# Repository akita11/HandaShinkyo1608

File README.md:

# Handa Shinkyo 1608

Ken Nakagakiさん(@ken0324)さんの[半田心経](https://x.com/i/events/1101723254899834880)を参考に、はんだ付けのしやすい1608サイズ（インチ表記で0603サイズ）のチップ抵抗を使った半田心経基板です。1-2Ωのチップ抵抗276個とLEDを1個はんだづけして完成です。（LEDの向きに注意。小さい緑マーカがある側が、USB-C基板コネクタ側です）

部品リストとPCBA用の部品位置ファイルもあり、そのまま[JLCPCB](https://www.jlcpcb.com)にPCBA発注することもできます（チート）。

給電は、裏面のボタン電池(CR2032)または基板パターンを使ったUSB Type-Cで行います（※USB Type-Cコネクタ給電を使う場合は板厚0.6mで製造）。
（USB PD規格のACアダプタ等を使う場合は、裏面に5.1kΩの抵抗2個をとりつけます）

はんだ付けのお勤めをとおして心を安らげましょう。合掌。

ハッシュタグ: #半田心経

## Author

Junichi Akita (@akita11, akita@ifdl.jp)

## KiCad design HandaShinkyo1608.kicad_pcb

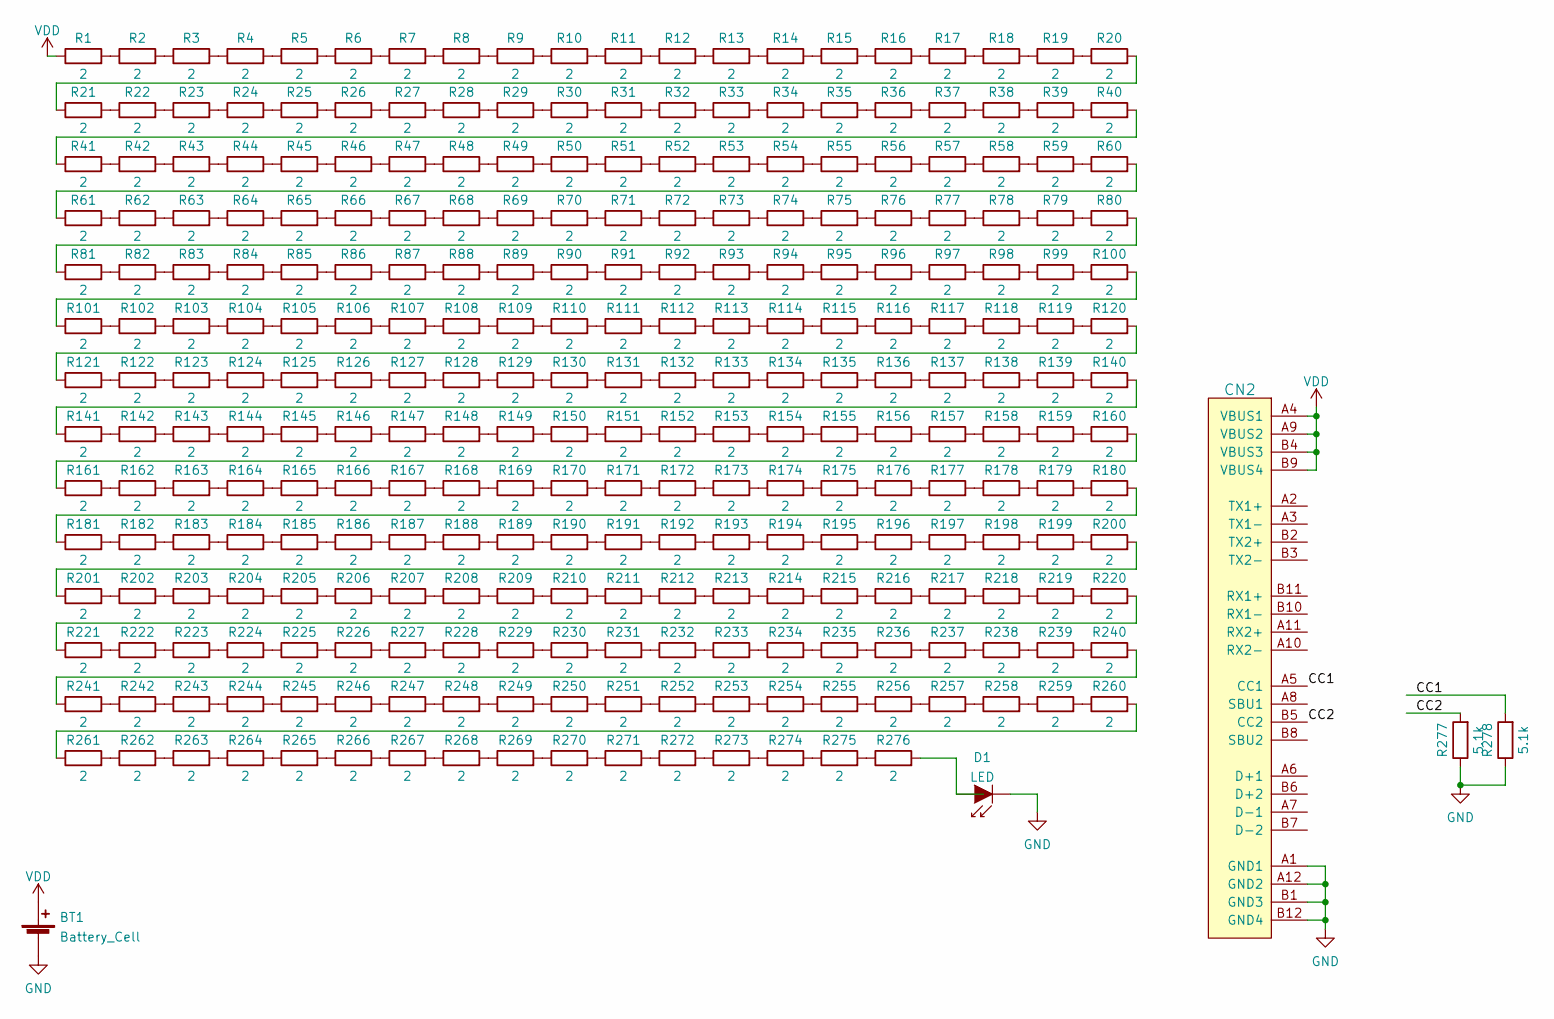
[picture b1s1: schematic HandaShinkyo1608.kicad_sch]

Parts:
BT1: Battery_Cell; BAT_CR2032_BC-2001
CN2: CON_USB-CPCBPLUG; USB-C_PCBPLUG
D1: LED; LED_0603_1608Metric
R1, R2, R3, R4, R5, R6, R7, R8, R9, R10, R11, R12, R13, R14, R15, R16, R17, R18, R19, R20, R21, R22, R23, R24, R25, R26, R27, R28, R29, R30, R31, R32, R33, R34, R35, R36, R37, R38, R39, R40, R41, R42, R43, R44, R45, R46, R47, R48, R49, R50, R51, R52, R53, R54, R55, R56, R57, R58, R59, R60, R61, R62, R63, R64, R65, R66, R67, R68, R69, R70, R71, R72, R73, R74, R75, R76, R77, R78, R79, R80, R81, R82, R83, R84, R85, R86, R87, R88, R89, R90, R91, R92, R93, R94, R95, R96, R97, R98, R99, R100, R101, R102, R103, R104, R105, R106, R107, R108, R109, R110, R111, R112, R113, R114, R115, R116, R117, R118, R119, R120, R121, R122, R123, R124, R125, R126, R127, R128, R129, R130, R131, R132, R133, R134, R135, R136, R137, R138, R139, R140, R141, R142, R143, R144, R145, R146, R147, R148, R149, R150, R151, R152, R153, R154, R155, R156, R157, R158, R159, R160, R161, R162, R163, R164, R165, R166, R167, R168, R169, R170, R171, R172, R173, R174, R175, R176, R177, R178, R179, R180, R181, R182, R183, R184, R185, R186, R187, R188, R189, R190, R191, R192, R193, R194, R195, R196, R197, R198, R199, R200, R201, R202, R203, R204, R205, R206, R207, R208, R209, R210, R211, R212, R213, R214, R215, R216, R217, R218, R219, R220, R221, R222, R223, R224, R225, R226, R227, R228, R229, R230, R231, R232, R233, R234, R235, R236, R237, R238, R239, R240, R241, R242, R243, R244, R245, R246, R247, R248, R249, R250, R251, R252, R253, R254, R255, R256, R257, R258, R259, R260, R261, R262, R263, R264, R265, R266, R267, R268, R269, R270, R271, R272, R273, R274, R275, R276: 2; R_0603_1608Metric
R277, R278: 5.1k; R_0603_1608Metric

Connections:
/CC1: CN2.A5 (CC1), R278.2
/CC2: CN2.B5 (CC2), R277.2
unnamed: D1.2 (A), R276.2
unnamed: R1.2, R2.1
unnamed: R2.2, R3.1
unnamed: R3.2, R4.1
unnamed: R4.2, R5.1
unnamed: R5.2, R6.1
unnamed: R6.2, R7.1
unnamed: R7.2, R8.1
unnamed: R8.2, R9.1
unnamed: R9.2, R10.1
unnamed: R10.2, R11.1
unnamed: R11.2, R12.1
unnamed: R12.2, R13.1
unnamed: R13.2, R14.1
unnamed: R14.2, R15.1
unnamed: R15.2, R16.1
unnamed: R16.2, R17.1
unnamed: R17.2, R18.1
unnamed: R18.2, R19.1
unnamed: R19.2, R20.1
unnamed: R20.2, R21.1
unnamed: R21.2, R22.1
unnamed: R22.2, R23.1
unnamed: R23.2, R24.1
unnamed: R24.2, R25.1
unnamed: R25.2, R26.1
unnamed: R26.2, R27.1
unnamed: R27.2, R28.1
unnamed: R28.2, R29.1
unnamed: R29.2, R30.1
unnamed: R30.2, R31.1
unnamed: R31.2, R32.1
unnamed: R32.2, R33.1
unnamed: R33.2, R34.1
unnamed: R34.2, R35.1
unnamed: R35.2, R36.1
unnamed: R36.2, R37.1
unnamed: R37.2, R38.1
unnamed: R38.2, R39.1
unnamed: R39.2, R40.1
unnamed: R40.2, R41.1
unnamed: R41.2, R42.1
unnamed: R42.2, R43.1
unnamed: R43.2, R44.1
unnamed: R44.2, R45.1
unnamed: R45.2, R46.1
unnamed: R46.2, R47.1
unnamed: R47.2, R48.1
unnamed: R48.2, R49.1
unnamed: R49.2, R50.1
unnamed: R50.2, R51.1
unnamed: R51.2, R52.1
unnamed: R52.2, R53.1
unnamed: R53.2, R54.1
unnamed: R54.2, R55.1
unnamed: R55.2, R56.1
unnamed: R56.2, R57.1
unnamed: R57.2, R58.1
unnamed: R58.2, R59.1
unnamed: R59.2, R60.1
unnamed: R60.2, R61.1
unnamed: R61.2, R62.1
unnamed: R62.2, R63.1
unnamed: R63.2, R64.1
unnamed: R64.2, R65.1
unnamed: R65.2, R66.1
unnamed: R66.2, R67.1
unnamed: R67.2, R68.1
unnamed: R68.2, R69.1
unnamed: R69.2, R70.1
unnamed: R70.2, R71.1
unnamed: R71.2, R72.1
unnamed: R72.2, R73.1
unnamed: R73.2, R74.1
unnamed: R74.2, R75.1
unnamed: R75.2, R76.1
unnamed: R76.2, R77.1
unnamed: R77.2, R78.1
unnamed: R78.2, R79.1
unnamed: R79.2, R80.1
unnamed: R80.2, R81.1
unnamed: R81.2, R82.1
unnamed: R82.2, R83.1
unnamed: R83.2, R84.1
unnamed: R84.2, R85.1
unnamed: R85.2, R86.1
unnamed: R86.2, R87.1
unnamed: R87.2, R88.1
unnamed: R88.2, R89.1
unnamed: R89.2, R90.1
unnamed: R90.2, R91.1
unnamed: R91.2, R92.1
unnamed: R92.2, R93.1
unnamed: R93.2, R94.1
unnamed: R94.2, R95.1
unnamed: R95.2, R96.1
unnamed: R96.2, R97.1
unnamed: R97.2, R98.1
unnamed: R98.2, R99.1
unnamed: R99.2, R100.1
unnamed: R100.2, R101.1
unnamed: R101.2, R102.1
unnamed: R102.2, R103.1
unnamed: R103.2, R104.1
unnamed: R104.2, R105.1
unnamed: R105.2, R106.1
unnamed: R106.2, R107.1
unnamed: R107.2, R108.1
unnamed: R108.2, R109.1
unnamed: R109.2, R110.1
unnamed: R110.2, R111.1
unnamed: R111.2, R112.1
unnamed: R112.2, R113.1
unnamed: R113.2, R114.1
unnamed: R114.2, R115.1
unnamed: R115.2, R116.1
unnamed: R116.2, R117.1
unnamed: R117.2, R118.1
unnamed: R118.2, R119.1
unnamed: R119.2, R120.1
unnamed: R120.2, R121.1
unnamed: R121.2, R122.1
unnamed: R122.2, R123.1
unnamed: R123.2, R124.1
unnamed: R124.2, R125.1
unnamed: R125.2, R126.1
unnamed: R126.2, R127.1
unnamed: R127.2, R128.1
unnamed: R128.2, R129.1
unnamed: R129.2, R130.1
unnamed: R130.2, R131.1
unnamed: R131.2, R132.1
unnamed: R132.2, R133.1
unnamed: R133.2, R134.1
unnamed: R134.2, R135.1
unnamed: R135.2, R136.1
unnamed: R136.2, R137.1
unnamed: R137.2, R138.1
unnamed: R138.2, R139.1
unnamed: R139.2, R140.1
unnamed: R140.2, R141.1
unnamed: R141.2, R142.1
unnamed: R142.2, R143.1
unnamed: R143.2, R144.1
unnamed: R144.2, R145.1
unnamed: R145.2, R146.1
unnamed: R146.2, R147.1
unnamed: R147.2, R148.1
unnamed: R148.2, R149.1
unnamed: R149.2, R150.1
unnamed: R150.2, R151.1
unnamed: R151.2, R152.1
unnamed: R152.2, R153.1
unnamed: R153.2, R154.1
unnamed: R154.2, R155.1
unnamed: R155.2, R156.1
unnamed: R156.2, R157.1
unnamed: R157.2, R158.1
unnamed: R158.2, R159.1
unnamed: R159.2, R160.1
unnamed: R160.2, R161.1
unnamed: R161.2, R162.1
unnamed: R162.2, R163.1
unnamed: R163.2, R164.1
unnamed: R164.2, R165.1
unnamed: R165.2, R166.1
unnamed: R166.2, R167.1
unnamed: R167.2, R168.1
unnamed: R168.2, R169.1
unnamed: R169.2, R170.1
unnamed: R170.2, R171.1
unnamed: R171.2, R172.1
unnamed: R172.2, R173.1
unnamed: R173.2, R174.1
unnamed: R174.2, R175.1
unnamed: R175.2, R176.1
unnamed: R176.2, R177.1
unnamed: R177.2, R178.1
unnamed: R178.2, R179.1
unnamed: R179.2, R180.1
unnamed: R180.2, R181.1
unnamed: R181.2, R182.1
unnamed: R182.2, R183.1
unnamed: R183.2, R184.1
unnamed: R184.2, R185.1
unnamed: R185.2, R186.1
unnamed: R186.2, R187.1
unnamed: R187.2, R188.1
unnamed: R188.2, R189.1
unnamed: R189.2, R190.1
unnamed: R190.2, R191.1
unnamed: R191.2, R192.1
unnamed: R192.2, R193.1
unnamed: R193.2, R194.1
unnamed: R194.2, R195.1
unnamed: R195.2, R196.1
unnamed: R196.2, R197.1
unnamed: R197.2, R198.1
unnamed: R198.2, R199.1
unnamed: R199.2, R200.1
unnamed: R200.2, R201.1
unnamed: R201.2, R202.1
unnamed: R202.2, R203.1
unnamed: R203.2, R204.1
unnamed: R204.2, R205.1
unnamed: R205.2, R206.1
unnamed: R206.2, R207.1
unnamed: R207.2, R208.1
unnamed: R208.2, R209.1
unnamed: R209.2, R210.1
unnamed: R210.2, R211.1
unnamed: R211.2, R212.1
unnamed: R212.2, R213.1
unnamed: R213.2, R214.1
unnamed: R214.2, R215.1
unnamed: R215.2, R216.1
unnamed: R216.2, R217.1
unnamed: R217.2, R218.1
unnamed: R218.2, R219.1
unnamed: R219.2, R220.1
unnamed: R220.2, R221.1
unnamed: R221.2, R222.1
unnamed: R222.2, R223.1
unnamed: R223.2, R224.1
unnamed: R224.2, R225.1
unnamed: R225.2, R226.1
unnamed: R226.2, R227.1
unnamed: R227.2, R228.1
unnamed: R228.2, R229.1
unnamed: R229.2, R230.1
unnamed: R230.2, R231.1
unnamed: R231.2, R232.1
unnamed: R232.2, R233.1
unnamed: R233.2, R234.1
unnamed: R234.2, R235.1
unnamed: R235.2, R236.1
unnamed: R236.2, R237.1
unnamed: R237.2, R238.1
unnamed: R238.2, R239.1
unnamed: R239.2, R240.1
unnamed: R240.2, R241.1
unnamed: R241.2, R242.1
unnamed: R242.2, R243.1
unnamed: R243.2, R244.1
unnamed: R244.2, R245.1
unnamed: R245.2, R246.1
unnamed: R246.2, R247.1
unnamed: R247.2, R248.1
unnamed: R248.2, R249.1
unnamed: R249.2, R250.1
unnamed: R250.2, R251.1
unnamed: R251.2, R252.1
unnamed: R252.2, R253.1
unnamed: R253.2, R254.1
unnamed: R254.2, R255.1
unnamed: R255.2, R256.1
unnamed: R256.2, R257.1
unnamed: R257.2, R258.1
unnamed: R258.2, R259.1
unnamed: R259.2, R260.1
unnamed: R260.2, R261.1
unnamed: R261.2, R262.1
unnamed: R262.2, R263.1
unnamed: R263.2, R264.1
unnamed: R264.2, R265.1
unnamed: R265.2, R266.1
unnamed: R266.2, R267.1
unnamed: R267.2, R268.1
unnamed: R268.2, R269.1
unnamed: R269.2, R270.1
unnamed: R270.2, R271.1
unnamed: R271.2, R272.1
unnamed: R272.2, R273.1
unnamed: R273.2, R274.1
unnamed: R274.2, R275.1
unnamed: R275.2, R276.1
VDD: BT1.1 (+), CN2.A4 (VBUS1), CN2.A9 (VBUS2), CN2.B4 (VBUS3), CN2.B9 (VBUS4), R1.1

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
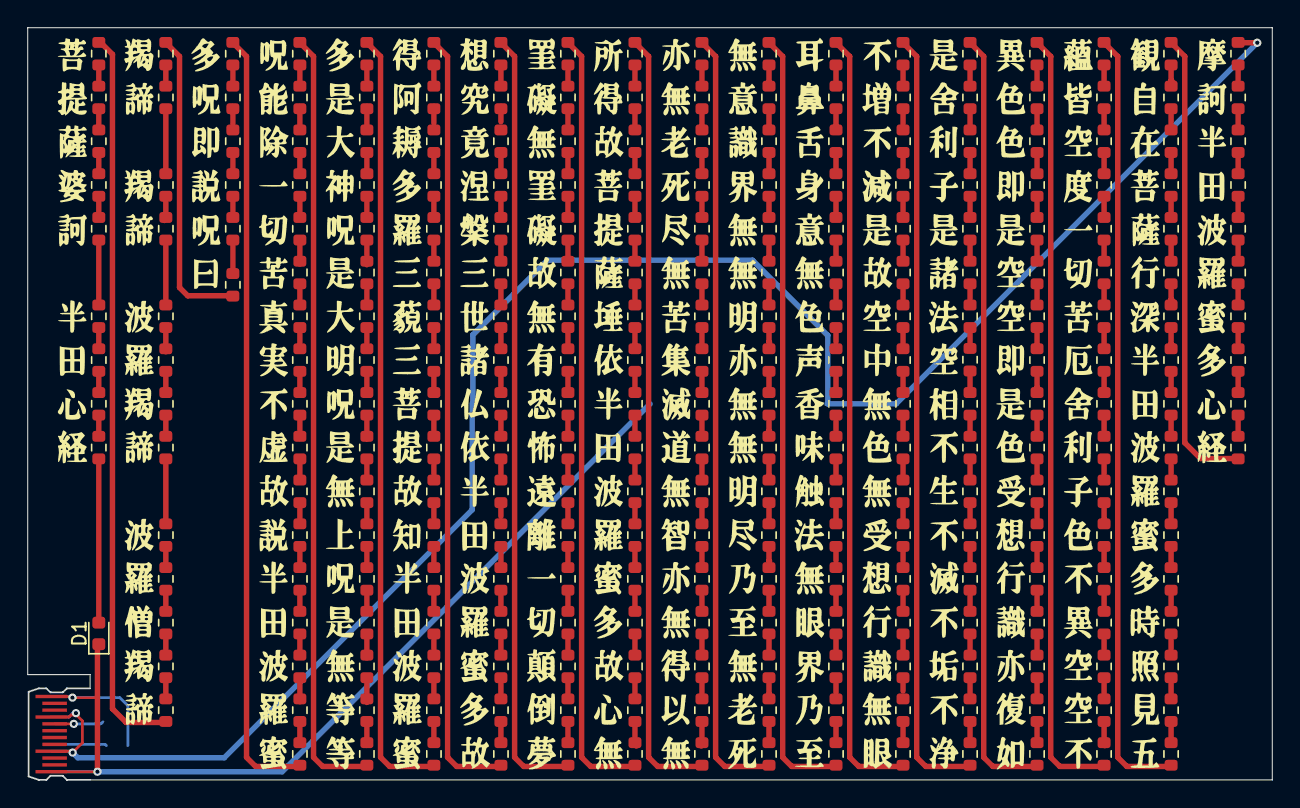
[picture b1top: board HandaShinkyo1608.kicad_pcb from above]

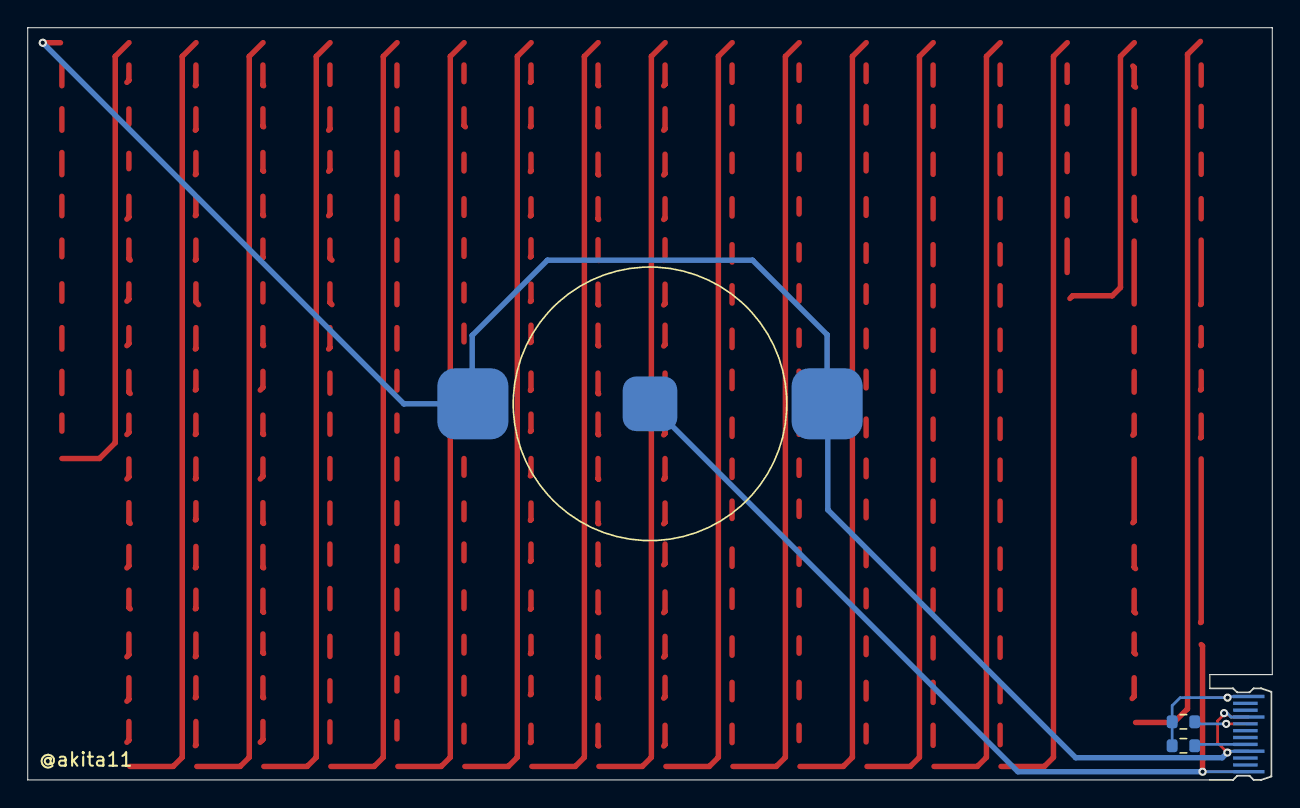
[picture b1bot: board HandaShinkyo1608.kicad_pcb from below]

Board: 2 copper layers, 91.0 x 55.0 mm, 281 parts (3 on the bottom side), 280 nets.

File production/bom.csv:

Designator,Footprint,Quantity,Value,LCSC Part #,
BT1,BAT_CR2032_BC-2001,1,Battery_Cell,C964830,¦ ÊBRCdrpB
D1,LED_0603_1608Metric,1,LED,C138546,
"R1, R10, R100, R101, R102, R103, R104, R105, R106, R107, R108, R109, R11, R110, R111, R112, R113, R114, R115, R116, R117, R118, R119, R12, R120, R121, R122, R123, R124, R125, R126, R127, R128, R129, R13, R130, R131, R132, R133, R134, R135, R136, R137, R138, R139, R14, R140, R141, R142, R143, R144, R145, R146, R147, R148, R149, R15, R150, R151, R152, R153, R154, R155, R156, R157, R158, R159, R16, R160, R161, R162, R163, R164, R165, R166, R167, R168, R169, R17, R170, R171, R172, R173, R174, R175, R176, R177, R178, R179, R18, R180, R181, R182, R183, R184, R185, R186, R187, R188, R189, R19, R190, R191, R192, R193, R194, R195, R196, R197, R198, R199, R2, R20, R200, R201, R202, R203, R204, R205, R206, R207, R208, R209, R21, R210, R211, R212, R213, R214, R215, R216, R217, R218, R219, R22, R220, R221, R222, R223, R224, R225, R226, R227, R228, R229, R23, R230, R231, R232, R233, R234, R235, R236, R237, R238, R239, R24, R240, R241, R242, R243, R244, R245, R246, R247, R248, R249, R25, R250, R251, R252, R253, R254, R255, R256, R257, R258, R259, R26, R260, R261, R262, R263, R264, R265, R266, R267, R268, R269, R27, R270, R271, R272, R273, R274, R275, R276, R28, R29, R3, R30, R31, R32, R33, R34, R35, R36, R37, R38, R39, R4, R40, R41, R42, R43, R44, R45, R46, R47, R48, R49, R5, R50, R51, R52, R53, R54, R55, R56, R57, R58, R59, R6, R60, R61, R62, R63, R64, R65, R66, R67, R68, R69, R7, R70, R71, R72, R73, R74, R75, R76, R77, R78, R79, R8, R80, R81, R82, R83, R84, R85, R86, R87, R88, R89, R9, R90, R91, R92, R93, R94, R95, R96, R97, R98, R99",R_0603_1608Metric,276,2,C2907139,
"R277, R278",R_0603_1608Metric,2,5.1k,C23186,¦USB-C{aðg¤êÌÝ

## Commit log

2024-11-20 add photo
2024-11-20 typo fix
2024-11-20 typo in README.md fixed
2024-11-25 update gerber (change on silk text)
2025-02-22 add 板厚
